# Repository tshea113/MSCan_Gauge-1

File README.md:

MSCan_Gauge
===========

This project uses a [Teensy 3.2 or 4.0 microcontroller](https://www.pjrc.com/teensy/index.html) to interface with a [Megasquirt open source standalone
engine controller](http://www.msextra.com/) via CAN bus. Data is received from the ECU and shown on a display that fits in a standard 52mm gauge pod.

Due to Teensy 3.2 availability, the project has been ported to work with [Teensy 4.0](https://www.pjrc.com/store/teensy40.html) which is both more powerful and more available. Highly suggest using that hardware over the Teensy 3.2.

## Demo
https://youtube.com/shorts/4NsZm0GjasA?feature=share

## Hardware used
* [Teensy 4.0 microcontroller](https://www.pjrc.com/store/teensy40.html)
* [Adafruit 128x64 monochrome 1.3" OLED display](http://www.adafruit.com/products/938) connected via SPI.
* [Adafruit rotary encoder](http://www.adafruit.com/products/377)

Unfortunately this display from Adafruit is pretty expensive compared to some of the cheaper no-name brands.
The gauge housing is fitted to work with this specific display model, but, although untested, any one of the SSD1306 driver controlled displays should work (as long as the screen is 128x64 pixels).

The rotary encoder is P/N: PEC11-4215F-S24 (or any substituteable encoder). If you are already ordering from Adafruit, it's best to just grab theirs.

## Libraries required
* [Metro](https://github.com/thomasfredericks/Metro-Arduino-Wiring) - event scheduling
* [Time](https://github.com/PaulStoffregen/Time) - onboard clock
* [FlexCAN_T4](https://github.com/tonton81/FlexCAN_T4) - CAN bus
* [SSD1306](https://github.com/adafruit/Adafruit_SSD1306) - OLED display
* [Adafruit GFX](https://github.com/adafruit/Adafruit-GFX-Library) - required by SSD1306
* [Adafruit BusIO](https://github.com/adafruit/Adafruit_BusIO) - I2C and SPI library (required by SSD1306)
* [EncoderTool](https://github.com/luni64/EncoderTool) - rotary encoder
* [Bounce2](https://github.com/thomasfredericks/Bounce2) - button debouncing

## Component BOM
Passives are 1206 package unless otherwise noted.
* R1 - 10K
* C1 - 10uF
* IC1 - SN65HVD230 (or similar) CAN transceiver
* VR1 - TSR 1-2450 DC/DC Converter (500mA may work but 1A is recommended)
* 2.54mm spacing male pin headers - standard length (5 male pins for OLED screen and 4 male pins for encoder)
* 2.54mm spacing female socket headers - standard length (2 banks of 14 female pins for the teensy)
* 8 way Molex Micro-fit+ connectors (Cable mount male and PCB mount female) and associated pins
* 5 and 4 position mating headers or connectors for OLED screen and encoder connections respectively

## Building the device

There are a lot of individual pieces that come together in this project, so it is best to test things as much as you can each step of the way. The gauge should come on when plugged into USB while external power is disconnected.
Before setting up CAN in your car, the gauge should still come on when the car is powered on and display a message about waiting for data. When you set up the CAN connection, you should start to see data come in on the screen.

### Software
You can use the released software to get a known working stable version. Install Teensyduino on your system and load the supplied hex file for your device. Plug in the teensy to your computer and press the program button on the Teensy and the software should be programmed.

If you would like to modify the code, you can build it yourself through Arduino IDE. You will need to install the listed libraries before building.

### PCB
Board gerber files are stored under Board files. Teensy 3.2 and Teensy 4.0 are *NOT* pin compatible, so choose the right PCB for your Teensy. Then encoder files are just for the rotary encoder which will be mounted remotely. I used OSHPark to build my boards, but there are plenty of PCB fabs out there to use.

The component BOM matches the labels on the PCB. You should be able to solder everything using a fine tip soldering iron. The CAN tranceiver is a little tricky, but doable.

### Housing
Highly recommended to print these out of ABS/ASA. I used PLA as a prototype and it *WILL* deform. Print the main housing using supports, but the PCB tray and the face should be able to just print flat on the print bed.

You will need the following fasteners:
* 8 M2 nuts
* 4 M2 bolts 6mm length
* 4 M2 bolts 10mm length

Fasten the PCB to the tray by placing 4 of the M2 nuts in the slots on the bottom. Use the shorter 6mm bolts to secure the PCB. The tray should slide right into the housing with the Molex connector coming out the back.
The tray may be tight at first, but sliding it in and out a few times should clearance it enough to be smooth.

Place 4 of the M2 Nuts into the back of the holes for the display mounts. Use a bolt to pull the nuts into their slots. Once they are in, they should be secure enough that they do not fall out.

To connect the display, you will need 5 female-to-female connectors. I used some pre-made 3 inch wires that have female header pins on the ends. Tuck the wires back into the gauge and place the screen into the slot.
Secure the display using the 10mm bolts. The gauge face should slot right into the housing.

### Car wiring
The wiring in the car should be wired up to the male Micro-fit+ connector. You will need to supply:
* 12V power
  * Preferably something that isn't hot while cranking.
  * This will probably be the same supply you use for other gauges like wideband.
* Ground
  * Nothing specific here, this isn't a sensor ground or anything.
* ENCG
  * This is the ground for the encoder. It should wire up to the corresponding pin on the encoder PCB.
* ENCB
  * This is the button pin for the encoder. It should wire up to the corresponding pin on the encoder PCB.
* ENC1
  * This is one of the direction pins for the encoder. It should wire up to the corresponding pin on the encoder PCB.
* ENC2
  * This is the other direction pin for the encoder. It should wire up to the corresponding pin on the encoder PCB.
* CANL
  * CAN low signal. This should wire up to the MegaSquirt.
* CANH
  * CAN high signal. This should wire up to the MegaSquirt.

CANL and CANH wires are a differential signal and should be twisted together coming from the ECU to whatever device you are connecting them to (in this case the gauge).

The CAN bus requires a 120Ohm termination at the end of the bus. I did not include this on the gauge, since other devices may already have this termination.
If this gauge is your only CAN device, you can use a Deutsh connector with this termination on the end:
* DTM06-2S-P006
  * This is the 120Ohm termination
* DTM04-2P
  * This is the female receptical.
  * You will also need pins and the little plastic bracket. Read more on Deutsch connectors to see what parts you need.

The Molex Micro-fit+ pins are very small and delicate. They do not require any special crimping tools, and I was able to use a generic pin crimping tool without issues. The pins should slot into the male housing and you will feel a click when they are secure.
If you aren't gentle with them, the wings on the end that secure the pins will get bent. To fix this, pull out the pin, carefully bend the wings back, and try again.

Connect the Molex connector to the gauge, and the gauge should come on when the ignition is in the ON position.

### Tunerstudio
You will need to configure CAN Realtime Data Broadcasting for the data you are interested in.
* Make sure the baseID is set to 1520.
* Data rate for each item will depend on how fast you expect the data to change. Things like coolant temp and MAT are going to be very slow while things like RPM and MAP are going to be faster.
* Be sure the master enable for CAN is set under CAN Paramteters
* Also enable CAN Broadcasting under CAN Broadcasting

## Future Development

There probably won't be any development on this project outside of bug fixes to make sure this stays in a good state.
I'm working on a new project that will allow me to fix some of the headaches with this design:
* Updating the diplay to use the GC9A01A circular LCD display.
  * LCDs are much easier to see in the sunlight and this display has RGB colors.
* Changing the project to use PlatformIO
  * This will allow the project to store libraries in GitHub. You will be able to sync the repo and build it directly!
  * I can use GitHub Actions to automate builds in the repo.
  * Lots of nice tools inside of PlatformIO IDE.
* Moving away from the Arduino style coding to something more C++ based.
  * Partially enabled by PlatformIO, since it just builds using CMake.
  * This project grew in scope enough where the lack of OOP was making it difficult to manage data & states.

New development will be under the teensy-CAN-gauge project: https://github.com/tshea113/teensy-CAN-gauge/

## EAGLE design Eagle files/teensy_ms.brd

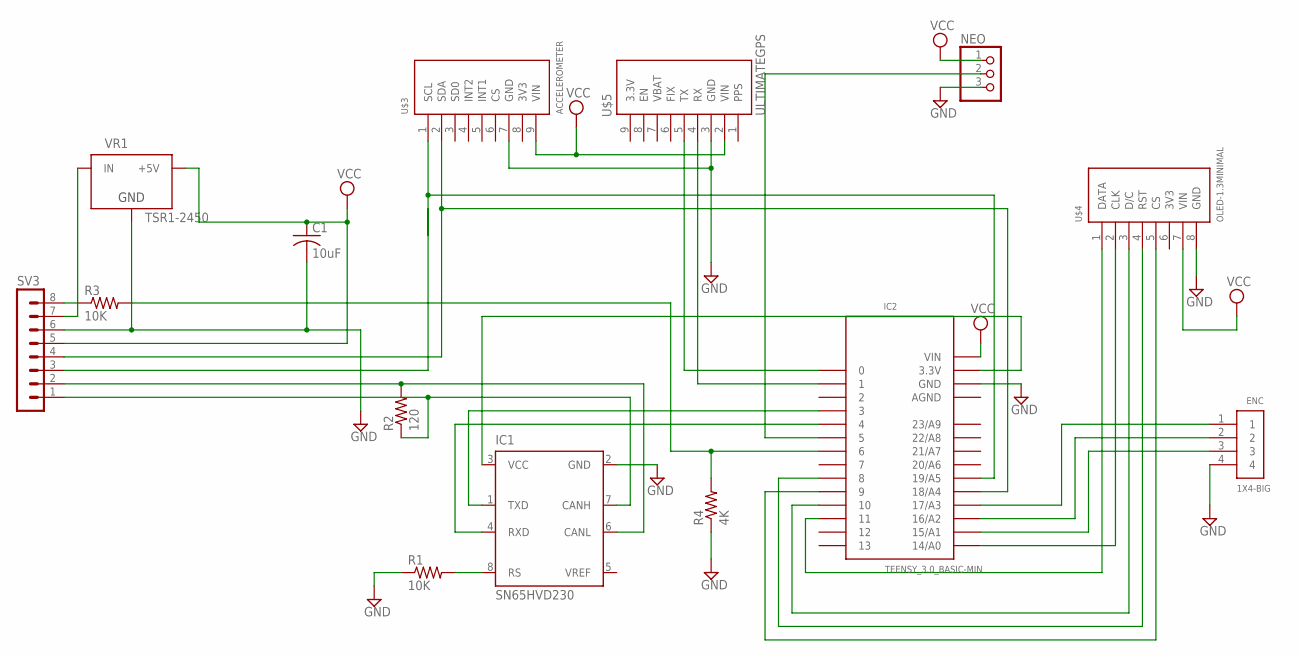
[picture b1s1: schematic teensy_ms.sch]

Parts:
C1: 10uF; C1206
ENC: 1X4-BIG; 1X04-BIG
IC1: SN65HVD230; SO8
IC2: TEENSY_3.0_BASIC-MIN; TEESNY_3.0_BASIC-MIN
NEO: PINHD-1X3; 1X03
R1, R3: 10K; M1206
R2: 120; M1206
R4: 4K; M1206
SV3: MA08-1
U$3: ACCELEROMETER
U$4: OLED-1.3MINIMAL; OLED-1.3-BARE
U$5: ULTIMATEGPS
VR1: TSR1-2450; TSR-1

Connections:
AGND: IC2.AGND
GND: C1.2, ENC.4, IC1.2 (GND), IC2.GND, NEO.3, R1.1, R4.1, SV3.6, U$3.7 (GND), U$4.8 (GND), U$5.3 (GND), VR1.2 (GND)
unnamed: IC1.8 (RS), R1.2
unnamed: IC1.3 (VCC), IC2.3.3V
unnamed: SV3.7, VR1.1 (IN)
unnamed: IC2.1, U$5.4 (RX)
unnamed: IC2.0, U$5.5 (TX)
unnamed: IC2.11, U$4.1 (DATA)
unnamed: IC2.14/A0, U$4.2 (CLK)
unnamed: IC2.10, U$4.3 (D/C)
unnamed: IC2.8, U$4.4 (RST)
unnamed: IC2.9, U$4.5 (CS)
unnamed: IC1.4 (RXD), IC2.4
unnamed: IC2.19/A5, SV3.3, U$3.1 (SCL)
unnamed: IC1.1 (TXD), IC2.3
unnamed: IC2.18/A4, SV3.4, U$3.2 (SDA)
unnamed: IC2.5, NEO.2
unnamed: IC1.7 (CANH), R2.1, SV3.1
unnamed: IC2.6, R3.2, R4.2
unnamed: IC1.6 (CANL), R2.2, SV3.2
unnamed: ENC.3, IC2.15/A1
unnamed: ENC.2, IC2.16/A2
unnamed: ENC.1, IC2.17/A3
unnamed: R3.1, SV3.8
VCC: C1.1, IC2.VIN, NEO.1, SV3.5, U$3.9 (VIN), U$4.7 (VIN), U$5.2 (VIN), VR1.3 (+5V)

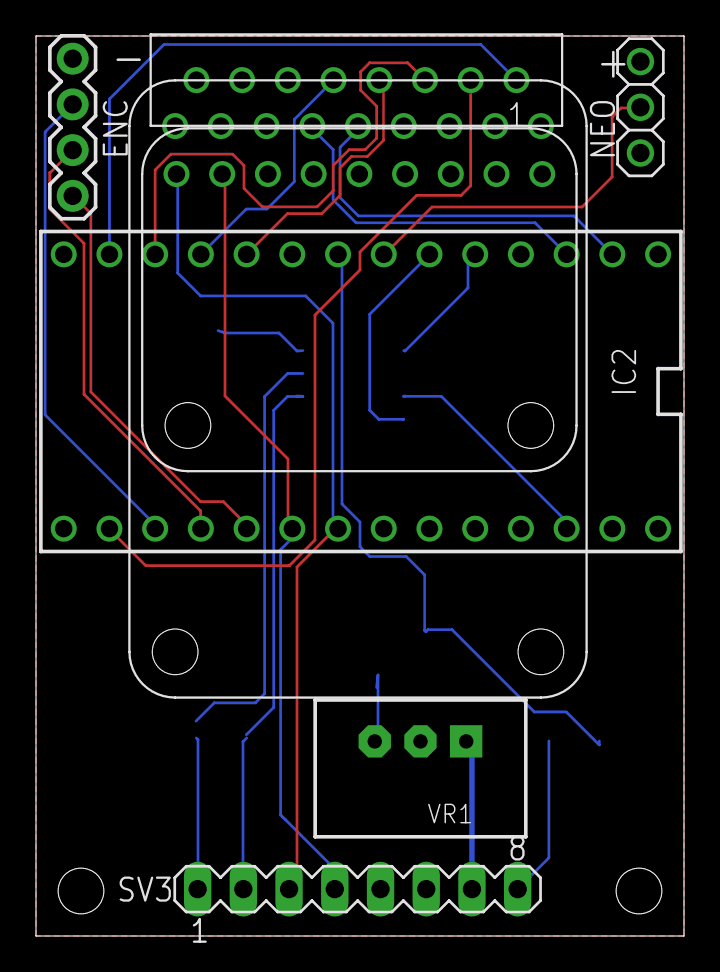
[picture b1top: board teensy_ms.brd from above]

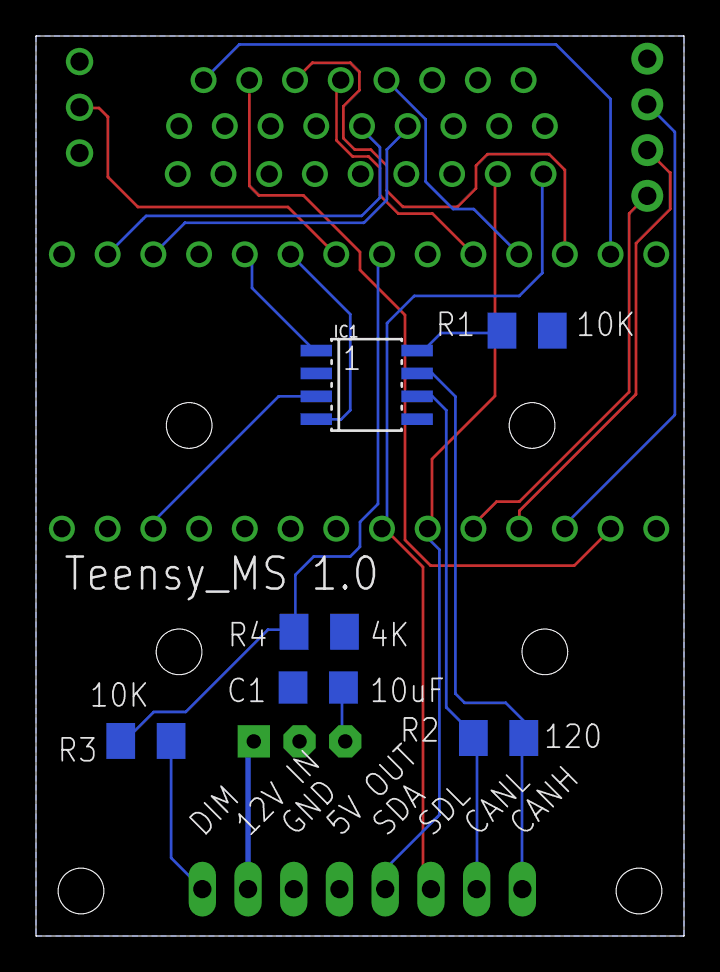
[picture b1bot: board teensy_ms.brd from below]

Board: 2 copper layers, 36.0 x 50.0 mm, 14 parts (6 on the bottom side), 24 nets.

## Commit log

2022-01-29 Remove GPS and Accel from PCB
2022-01-29 Add to gitignore
2022-01-29 Remove GPS and Accel. Clean up code.
2022-01-29 Update readme with removed gps and accel
2022-01-29 fix hyperlink in readme
2022-01-29 update gitignore
2022-01-29 Eliminate some magic numbers
2022-01-30 Add startup animation
2022-01-30 OLED changes
2022-02-01 Syntax fix
2022-02-08 Move arduino file for ide
2022-02-08 Fix build errors
2022-02-09 UI fixes
2022-02-10 Update flexCAN to newer fork.
2022-02-11 code refactoring
2022-02-11 More refactor
2022-02-11 code cleanup
2022-02-15 Misc code cleanup
2022-02-16 Finalize screen changes
2022-02-19 fix init animation brightness
2022-02-19 Add debug mode
2022-02-20 Update README.md
    Updating readme to credit original authors now that the fork has been detached.
2022-02-20 Add selection menu
2022-02-22 Add gauge changes
2022-02-23 Add settings
2022-02-24 change neopixel to led ring
2022-02-26 Add settings storage
2022-02-26 big changes
2022-02-26 fix warnings
2022-02-28 small fixes from last branch
2022-03-02 Add fusion360 files
2022-03-06 Change folder from fusion360 to board
2022-03-11 update to FlexCAN_t4
2022-03-11 update lib
2022-03-12 Add a comment for the flexcan init
2022-03-12 Add debug stuff
2022-03-12 Tech debt fixes
2022-03-12 Style and tech debt fixes
2022-03-12 fix todo
2022-03-12 Add pages to single and graph
2022-03-12 Change constant naming convention
2022-03-12 Fix constants
2022-03-12 int conventions
2022-03-12 stuff
2022-03-12 conventions
2022-03-12 fix files
2022-03-12 file name updates
2022-03-12 update includes
2022-03-12 alignment
2022-03-12 alignment display
2022-03-12 fix neopixel brightness
2022-03-15 change button debounce to library
2022-03-15 fix names that were off screen
2022-03-15 Update single gauge printing
2022-03-15 dead code cleanup
2022-03-16 misc syntax fixes
2022-10-23 Add watchdog
2022-10-23 fix the iac logic
2023-01-28 add pcb gerber files and remove f3d file
2023-01-29 fix bottom dashboard
2023-01-30 Update dashboard layout
2023-02-04 Move menu check out of display routine
2023-02-04 cleanup
2023-02-04 Add boost
2023-02-05 Fix highest value width issue
2023-02-05 Misc formatting
2023-02-05 Fix data casting for can messages
2023-02-05 Create LICENSE
    I came across this project through the msextra thread where you documented this work: https://www.msextra.com/forums/viewtopic.php?f=67&t=52539
    If your intention was to share this code as open source, it is good practice to add a software license to allow others to use this. I've selected a basic MIT license to add to this repo, feel free to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
2023-02-12 Add gauge housing
2023-02-12 remove LED pins from boards
2023-02-12 Remove led code
2023-02-12 remove led ring stuff from readme
2023-02-12 Fix faceplate
2023-07-15 Update boards with latest revision
2023-07-15 Remove old boards
2023-07-15 remove watchdog
2023-07-20 Move startup to beginning and increase delay.
2023-07-22 Add some more details to the readme
